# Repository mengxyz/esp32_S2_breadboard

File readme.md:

# Esp32 S2 Breadboard

| front                         | back                            |
| ----------------------------- | ------------------------------- |
|  |  |

# Specs

- 1 UART
- 1 OTG

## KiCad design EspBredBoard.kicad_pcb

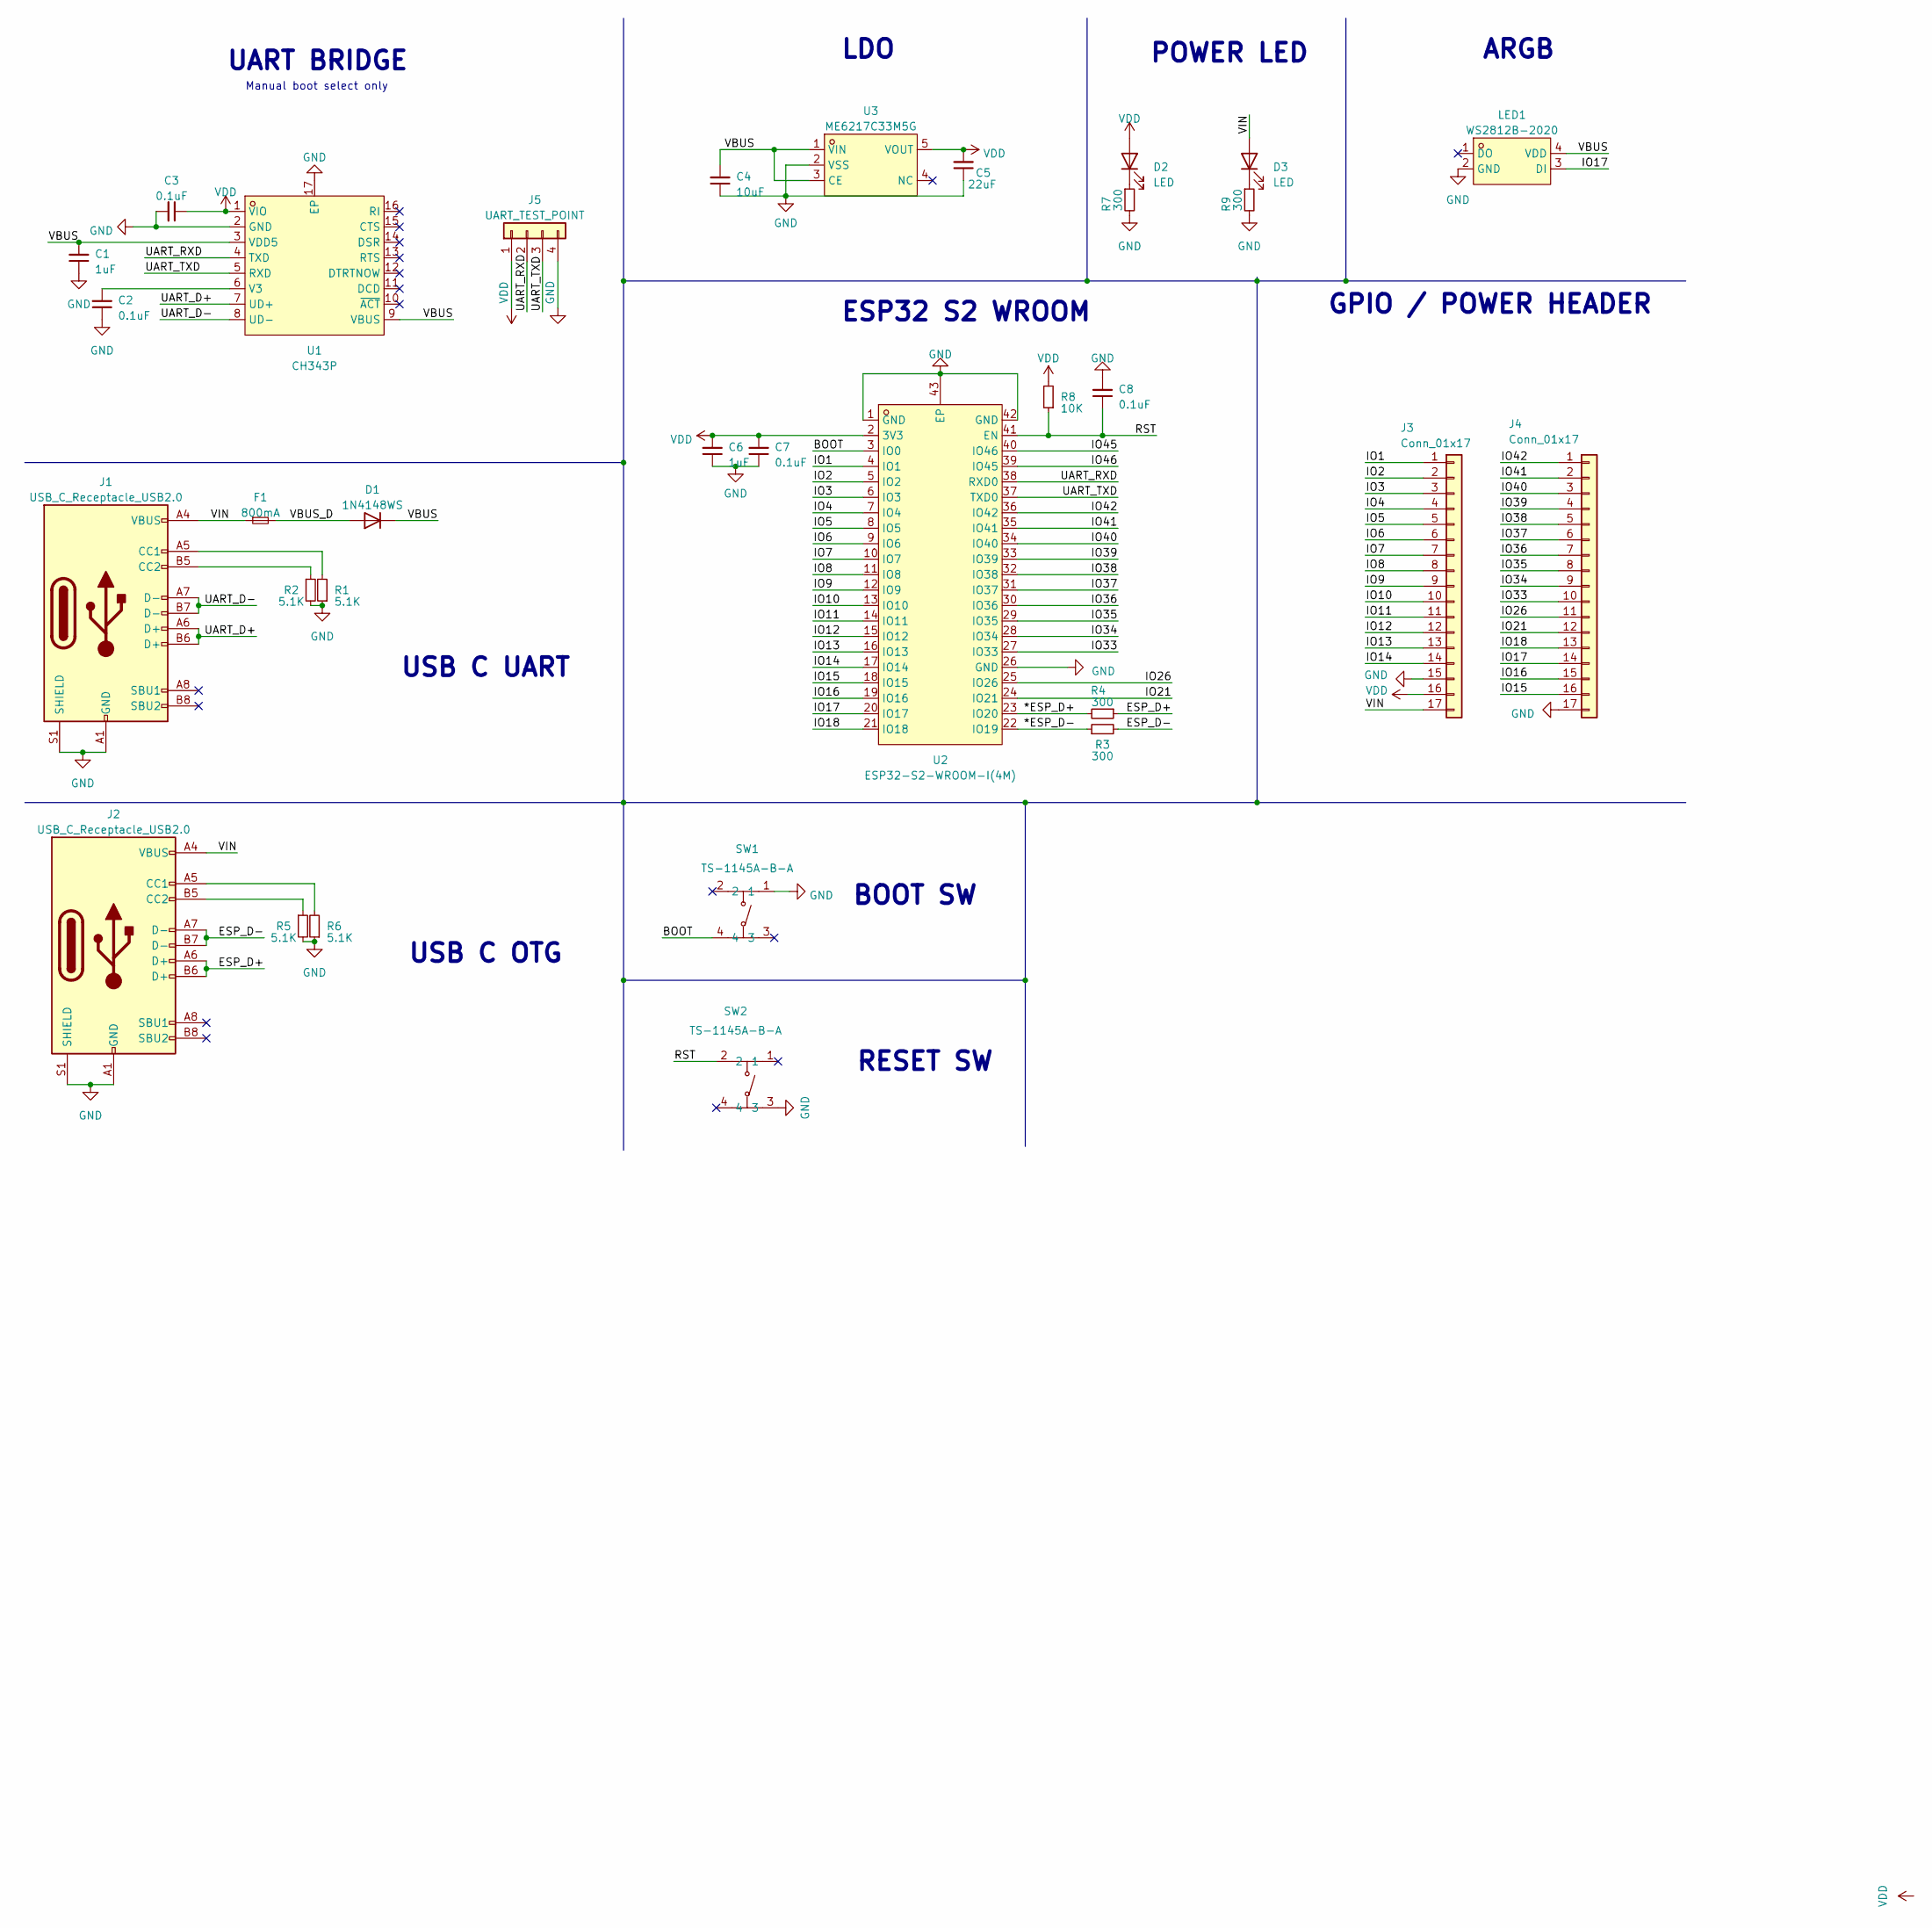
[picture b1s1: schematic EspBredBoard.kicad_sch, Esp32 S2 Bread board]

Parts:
C1, C6: 1uF; C_0603_1608Metric_Pad1.08x0.95mm_HandSolder
C2, C3, C7, C8: 0.1uF; C_0603_1608Metric_Pad1.08x0.95mm_HandSolder
C4: 10uF; C_1206_3216Metric_Pad1.33x1.80mm_HandSolder
C5: 22uF; C_1206_3216Metric_Pad1.33x1.80mm_HandSolder
D1: 1N4148WS; D_SOD-323_HandSoldering
D2, D3: LED; LED_0603_1608Metric_Pad1.05x0.95mm_HandSolder
F1: 800mA; Fuse_0805_2012Metric_Pad1.15x1.40mm_HandSolder
J1, J2: USB_C_Receptacle_USB2.0; USB_C_Receptacle_GCT_USB4105-xx-A_16P_TopMnt_Horizontal
J3, J4: Conn_01x17; PinHeader_1x17_P2.54mm_Vertical
J5: UART_TEST_POINT; PinHeader_1x04_P2.54mm_Vertical
LED1: WS2812B-2020; LED-SMD_4P-L2.0-W2.0-TL_WS2812B-2020; LCSC Part C965555
R1, R2, R5, R6: 5.1K; R_0603_1608Metric_Pad0.98x0.95mm_HandSolder
R3, R4, R7, R9: 300; R_0603_1608Metric_Pad0.98x0.95mm_HandSolder
R8: 10K; R_0603_1608Metric_Pad0.98x0.95mm_HandSolder
SW1, SW2: TS-1145A-B-A; SW-SMD_4P-L4.2-W3.2-P2.15-LS5.2; LCSC Part C318904
U1: CH343P; TQFN-16_L3.0-W3.0-P0.50-BL-EP1.7; LCSC Part C2846043
U2: ESP32-S2-WROOM-I(4M); WIFI-SMD_ESP32-S2-WROVER-I; LCSC Part C967026
U3: ME6217C33M5G; SOT-23-5_L3.0-W1.7-P0.95-LS2.8-BR; LCSC Part C427602

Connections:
/*ESP_D+: R4.2, U2.23 (IO20)
/*ESP_D-: R3.1, U2.22 (IO19)
/BOOT: SW1.4, U2.3 (IO0)
/ESP_D+: J2.A6 (D+), J2.B6 (D+), R4.1
/ESP_D-: J2.A7 (D-), J2.B7 (D-), R3.2
/IO1: J3.1, U2.4 (IO1)
/IO2: J3.2, U2.5 (IO2)
/IO3: J3.3, U2.6 (IO3)
/IO4: J3.4, U2.7 (IO4)
/IO5: J3.5, U2.8 (IO5)
/IO6: J3.6, U2.9 (IO6)
/IO7: J3.7, U2.10 (IO7)
/IO8: J3.8, U2.11 (IO8)
/IO9: J3.9, U2.12 (IO9)
/IO10: J3.10, U2.13 (IO10)
/IO11: J3.11, U2.14 (IO11)
/IO12: J3.12, U2.15 (IO12)
/IO13: J3.13, U2.16 (IO13)
/IO14: J3.14, U2.17 (IO14)
/IO15: J4.16, U2.18 (IO15)
/IO16: J4.15, U2.19 (IO16)
/IO17: J4.14, LED1.3 (DI), U2.20 (IO17)
/IO18: J4.13, U2.21 (IO18)
/IO21: J4.12, U2.24 (IO21)
/IO26: J4.11, U2.25 (IO26)
/IO33: J4.10, U2.27 (IO33)
/IO34: J4.9, U2.28 (IO34)
/IO35: J4.8, U2.29 (IO35)
/IO36: J4.7, U2.30 (IO36)
/IO37: J4.6, U2.31 (IO37)
/IO38: J4.5, U2.32 (IO38)
/IO39: J4.4, U2.33 (IO39)
/IO40: J4.3, U2.34 (IO40)
/IO41: J4.2, U2.35 (IO41)
/IO42: J4.1, U2.36 (IO42)
/IO45: U2.40 (IO46)
/IO46: U2.39 (IO45)
/RST: C8.1, R8.1, SW2.2, U2.41 (EN)
/UART_D+: J1.A6 (D+), J1.B6 (D+), U1.7 (UD+)
/UART_D-: J1.A7 (D-), J1.B7 (D-), U1.8 (UD-)
/UART_RXD: J5.2, U1.4 (TXD), U2.38 (RXD0)
/UART_TXD: J5.3, U1.5 (RXD), U2.37 (TXD0)
/VBUS: C1.2, C4.2, D1.1 (K), LED1.4 (VDD), U1.3 (VDD5), U1.9 (VBUS), U3.1 (VIN), U3.3 (CE)
/VBUS_D: D1.2 (A), F1.2
/VIN: D3.2 (A), F1.1, J1.A4 (VBUS), J1.A9 (VBUS), J1.B4 (VBUS), J1.B9 (VBUS), J2.A4 (VBUS), J2.A9 (VBUS), J2.B4 (VBUS), J2.B9 (VBUS), J3.17
GND: C1.1, C2.1, C3.2, C4.1, C5.1, C6.1, C7.1, C8.2, J1.A1 (GND), J1.A12 (GND), J1.B1 (GND), J1.B12 (GND), J1.S1 (SHIELD), J2.A1 (GND), J2.A12 (GND), J2.B1 (GND), J2.B12 (GND), J2.S1 (SHIELD), J3.15, J4.17, J5.4, LED1.2 (GND), R1.1, R2.2, R5.2, R6.1, R7.2, R9.2, SW1.1, SW2.3, U1.2 (GND), U1.17 (EP), U2.1 (GND), U2.26 (GND), U2.42 (GND), U2.43 (EP), U3.2 (VSS)
unnamed: D2.1 (K), R7.1
unnamed: D3.1 (K), R9.1
unnamed: J1.A5 (CC1), R1.2
unnamed: J1.B5 (CC2), R2.1
unnamed: J2.A5 (CC1), R6.2
unnamed: J2.B5 (CC2), R5.1
unnamed: C2.2, U1.6 (V3)
VDD: C3.1, C5.2, C6.2, C7.2, D2.2 (A), J3.16, J5.1, R8.2, U1.1 (VIO), U2.2 (3V3), U3.5 (VOUT)

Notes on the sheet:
POWER LED
LDO
GPIO / POWER HEADER
USB C OTG
ARGB
USB C UART
RESET SW
ESP32 S2 WROOM
BOOT SW
UART BRIDGE
Manual boot select only

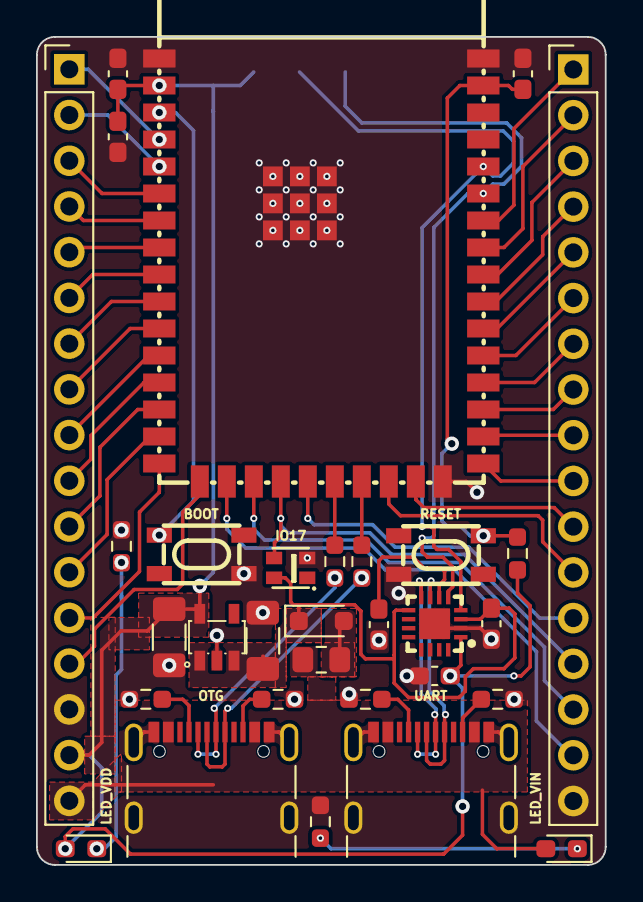
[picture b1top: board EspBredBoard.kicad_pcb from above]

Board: 2 copper layers, 31.6 x 46.0 mm, 32 parts (1 on the bottom side), 52 nets.

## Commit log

2024-12-26 fix wrong uart route - add uart test point - add vin led
